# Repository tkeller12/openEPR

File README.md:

# openEPR
Open-Source EPR Spectrometer

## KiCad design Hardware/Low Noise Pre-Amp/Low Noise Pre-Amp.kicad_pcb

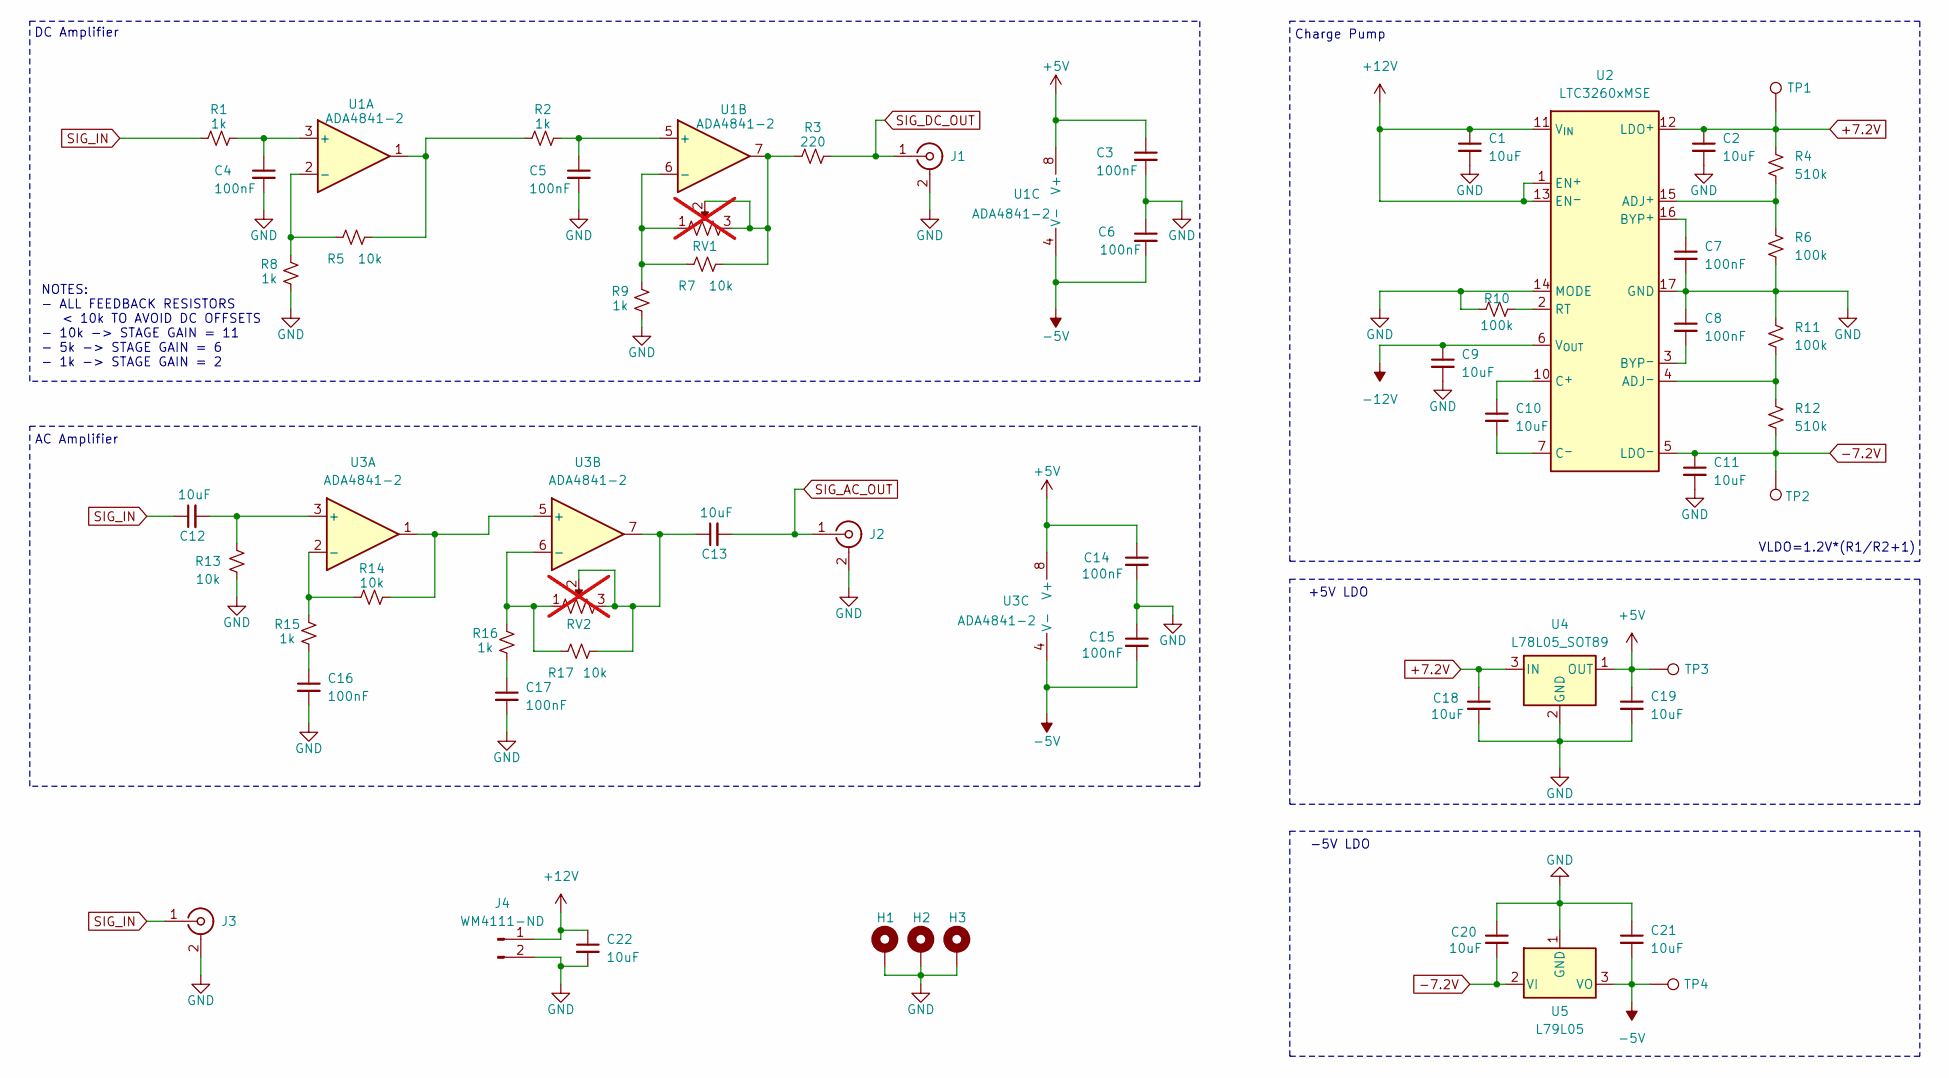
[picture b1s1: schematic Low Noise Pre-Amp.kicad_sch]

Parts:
C1, C2, C9, C10, C11, C12, C13, C18, C19, C20, C21, C22: 10uF; C_0805_2012Metric; MPN GRM21BR61H106KE43L; Digikey 490-18663-1-ND
C3, C4, C5, C6, C7, C8, C14, C15, C16, C17: 100nF; C_0805_2012Metric; MPN C0805C104K5RACTU; Digikey 399-C0805C104K5RACTUCT-ND
H1, H2, H3: M3; MountingHole_3.2mm_M3_DIN965_Pad
J1, J2, J3: RF2-152-T-00-50-G-HDW; SMA_Wurth_60312002114503_Vertical; MPN RF2-152-T-00-50-G-HDW; Digikey 2057-RF2-152-T-00-50-G-HDW-ND
J4: WM4111-ND; Molex_KK-254_AE-6410-02A_1x02_P2.54mm_Vertical; MPN 0022272021; Digikey WM4111-ND
R1, R2, R8, R9, R15, R16: 1k; R_0805_2012Metric; MPN RC0805FR-071KL; Digikey 311-1.00KCRCT-ND
R3: 220; R_0805_2012Metric; MPN RC0805FR-07220RL; Digikey 311-220CRCT-ND
R4, R12: 510k; R_0805_2012Metric; MPN RC0805FR-13510KL; Digikey 13-RC0805FR-13510KLCT-ND
R5, R7, R13, R14, R17: 10k; R_0805_2012Metric; MPN RC0805FR-0710KL; Digikey 311-10.0KCRCT-ND
R6, R10, R11: 100k; R_0805_2012Metric; MPN RC0805FR-07100KL; Digikey 311-100KCRCT-ND
RV1, RV2: R_Potentiometer_US; PinHeader_1x03_P2.54mm_Vertical; not fitted
TP1, TP2, TP3, TP4: TestPoint; TestPoint_Pad_D1.0mm
U1, U3: ADA4841-2; SOIC-8_3.9x4.9mm_P1.27mm; MPN ADA4841-2YRZ-R7; Digikey 505-ADA4841-2YRZ-R7CT-ND
U2: LTC3260xMSE; MSOP-16-1EP_3x4.039mm_P0.5mm_EP1.651x2.845mm_ThermalVias; MPN LTC3260EMSE#TRPBF; Digikey LTC3260EMSE#TRPBFCT-ND
U4: L78L05_SOT89; SOT-89-3; MPN L78L05ABUTR; Digikey 497-1181-1-ND
U5: L79L05; SOT-89-3; MPN L79L05ABUTR; Digikey 497-1217-1-ND

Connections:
+5V: C3.1, C14.1, C19.1, TP3.1, U1.8 (V+), U3.8 (V+), U4.1 (OUT)
+7.2V: C2.1, C18.1, R4.1, TP1.1, U2.12 (LDO^{+}), U4.3 (IN)
+12V: C1.1, C22.1, J4.1, U2.1 (EN^{+}), U2.11 (V_{IN}), U2.13 (EN^{-})
-5V: C6.2, C15.2, C21.2, TP4.1, U1.4 (V-), U3.4 (V-), U5.3 (VO)
-7.2V: C11.1, C20.2, R12.2, TP2.1, U2.5 (LDO^{-}), U5.2 (VI)
-12V: C9.1, U2.6 (V_{OUT})
GND: C1.2, C2.2, C3.2, C4.2, C5.2, C6.1, C7.2, C8.1, C9.2, C11.2, C14.2, C15.1, C16.2, C17.2, C18.2, C19.2, C20.1, C21.1, C22.2, H1.1, H2.1, H3.1, J1.2 (Ext), J2.2 (Ext), J3.2 (Ext), J4.2, R6.2, R8.1, R9.1, R10.2, R11.1, R13.1, U2.14 (MODE), U2.17 (GND), U4.2 (GND), U5.1 (GND)
unnamed: C13.1, R17.1, RV2.2, RV2.3, U3.7
unnamed: C16.1, R15.1
unnamed: C17.1, R16.1
unnamed: R2.1, R5.1, U1.1
unnamed: R3.1, R7.1, RV1.2, RV1.3, U1.7
unnamed: C4.1, R1.2, U1.3 (+)
unnamed: R5.2, R8.2, U1.2 (-)
unnamed: C5.1, R2.2, U1.5 (+)
unnamed: R7.2, R9.2, RV1.1, U1.6 (-)
unnamed: R4.2, R6.1, U2.15 (ADJ^{+})
unnamed: R11.2, R12.1, U2.4 (ADJ^{-})
unnamed: C7.1, U2.16 (BYP^{+})
unnamed: C8.2, U2.3 (BYP^{-})
unnamed: C10.1, U2.10 (C^{+})
unnamed: C10.2, U2.7 (C^{-})
unnamed: R10.1, U2.2 (RT)
unnamed: C12.2, R13.2, U3.3 (+)
unnamed: R14.1, R15.2, U3.2 (-)
unnamed: R14.2, U3.1, U3.5 (+)
unnamed: R16.2, R17.2, RV2.1, U3.6 (-)
SIG_AC_OUT: C13.2, J2.1 (In)
SIG_DC_OUT: J1.1 (In), R3.2
SIG_IN: C12.1, J3.1 (In), R1.1

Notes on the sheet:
+5V LDO
-5V LDO
Charge Pump
NOTES: - ALL FEEDBACK RESISTORS < 10k TO AVOID DC OFFSETS - 10k -> STAGE GAIN = 11 - 5k -> STAGE GAIN = 6 - 1k -> STAGE GAIN = 2
AC Amplifier
VLDO=1.2V*(R1/R2+1)
DC Amplifier

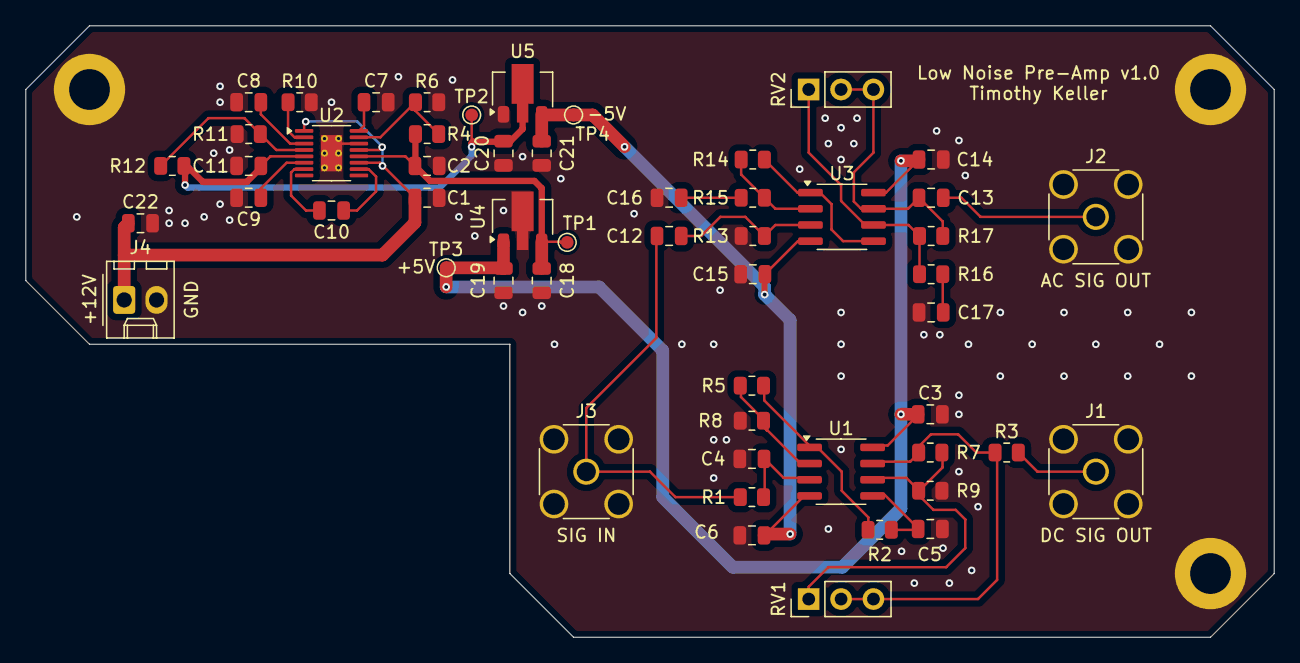
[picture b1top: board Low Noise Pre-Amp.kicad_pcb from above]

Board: 2 copper layers, 98.0 x 48.0 mm, 57 parts (0 on the bottom side), 30 nets.

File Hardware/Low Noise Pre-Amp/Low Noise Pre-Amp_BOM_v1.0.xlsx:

# | Reference | Qty | Value | DNP | Footprint | Description | Digikey | Manufacturer | MPN
1 | C1,C2,C9,C10,C11,C12,C13,C18,C19,C20,C21,C22 | 12 | 10uF |  | Capacitor_SMD:C_0805_2012Metric | Unpolarized capacitor, small symbol | 490-18663-1-ND | Murata Electronics | GRM21BR61H106KE43L
2 | C3,C4,C5,C6,C7,C8,C14,C15,C16,C17 | 10 | 100nF |  | Capacitor_SMD:C_0805_2012Metric | Unpolarized capacitor, small symbol | 399-C0805C104K5RACTUCT-ND | KEMET | C0805C104K5RACTU
3 | J1,J2,J3 | 3 | RF2-152-T-00-50-G-HDW |  | Connector_Coaxial:SMA_Wurth_60312002114503_Vertical | SMA JACK STR PCB 50OHM 18GHZ BRS | 2057-RF2-152-T-00-50-G-HDW-ND | Adam Tech | RF2-152-T-00-50-G-HDW
4 | J4 | 1 | WM4111-ND |  | Connector_Molex:Molex_KK-254_AE-6410-02A_1x02_P2.54mm_Vertical | CONN HEADER VERT 2POS 2.54MM | WM4111-ND | Molex | 0022272021
5 | R1,R2,R8,R9,R15,R16 | 6 | 1k |  | Resistor_SMD:R_0805_2012Metric | Resistor, small US symbol | 311-1.00KCRCT-ND | YAGEO | RC0805FR-071KL
6 | R3 | 1 | 220 |  | Resistor_SMD:R_0805_2012Metric | Resistor, small US symbol | 311-220CRCT-ND | YAGEO | RC0805FR-07220RL
7 | R4,R12 | 2 | 510k |  | Resistor_SMD:R_0805_2012Metric | Resistor, small US symbol | 13-RC0805FR-13510KLCT-ND | YAGEO | RC0805FR-13510KL
8 | R5,R7,R13,R14,R17 | 5 | 10k |  | Resistor_SMD:R_0805_2012Metric | Resistor, small US symbol | 311-10.0KCRCT-ND | YAGEO | RC0805FR-0710KL
9 | R6,R10,R11 | 3 | 100k |  | Resistor_SMD:R_0805_2012Metric | Resistor, small US symbol | 311-100KCRCT-ND | YAGEO | RC0805FR-07100KL
10 | RV1,RV2 | 2 | R_Potentiometer_US | DNP | Connector_PinHeader_2.54mm:PinHeader_1x03_P2.54mm_Vertical | Potentiometer, US symbol
11 | U1,U3 | 2 | ADA4841-2 |  | Package_SO:SOIC-8_3.9x4.9mm_P1.27mm | IC OPAMP GP 2 CIRCUIT 8SOIC | 505-ADA4841-2YRZ-R7CT-ND | Analog Devices Inc. | ADA4841-2YRZ-R7
12 | U2 | 1 | LTC3260xMSE |  | Package_SO:MSOP-16-1EP_3x4.039mm_P0.5mm_EP1.651x2.845mm_ThermalVias | IC REG CHARGE PUMP INV DL 16MSOP | LTC3260EMSE#TRPBFCT-ND | Analog Devices Inc. | LTC3260EMSE#TRPBF
13 | U4 | 1 | L78L05_SOT89 |  | Package_TO_SOT_SMD:SOT-89-3 | IC REG LINEAR 5V 100MA SOT89-3 | 497-1181-1-ND | STMicroelectronics | L78L05ABUTR
14 | U5 | 1 | L79L05 |  | Package_TO_SOT_SMD:SOT-89-3 | IC REG LINEAR -5V 100MA SOT89-3 | 497-1217-1-ND | STMicroelectronics | L79L05ABUTR

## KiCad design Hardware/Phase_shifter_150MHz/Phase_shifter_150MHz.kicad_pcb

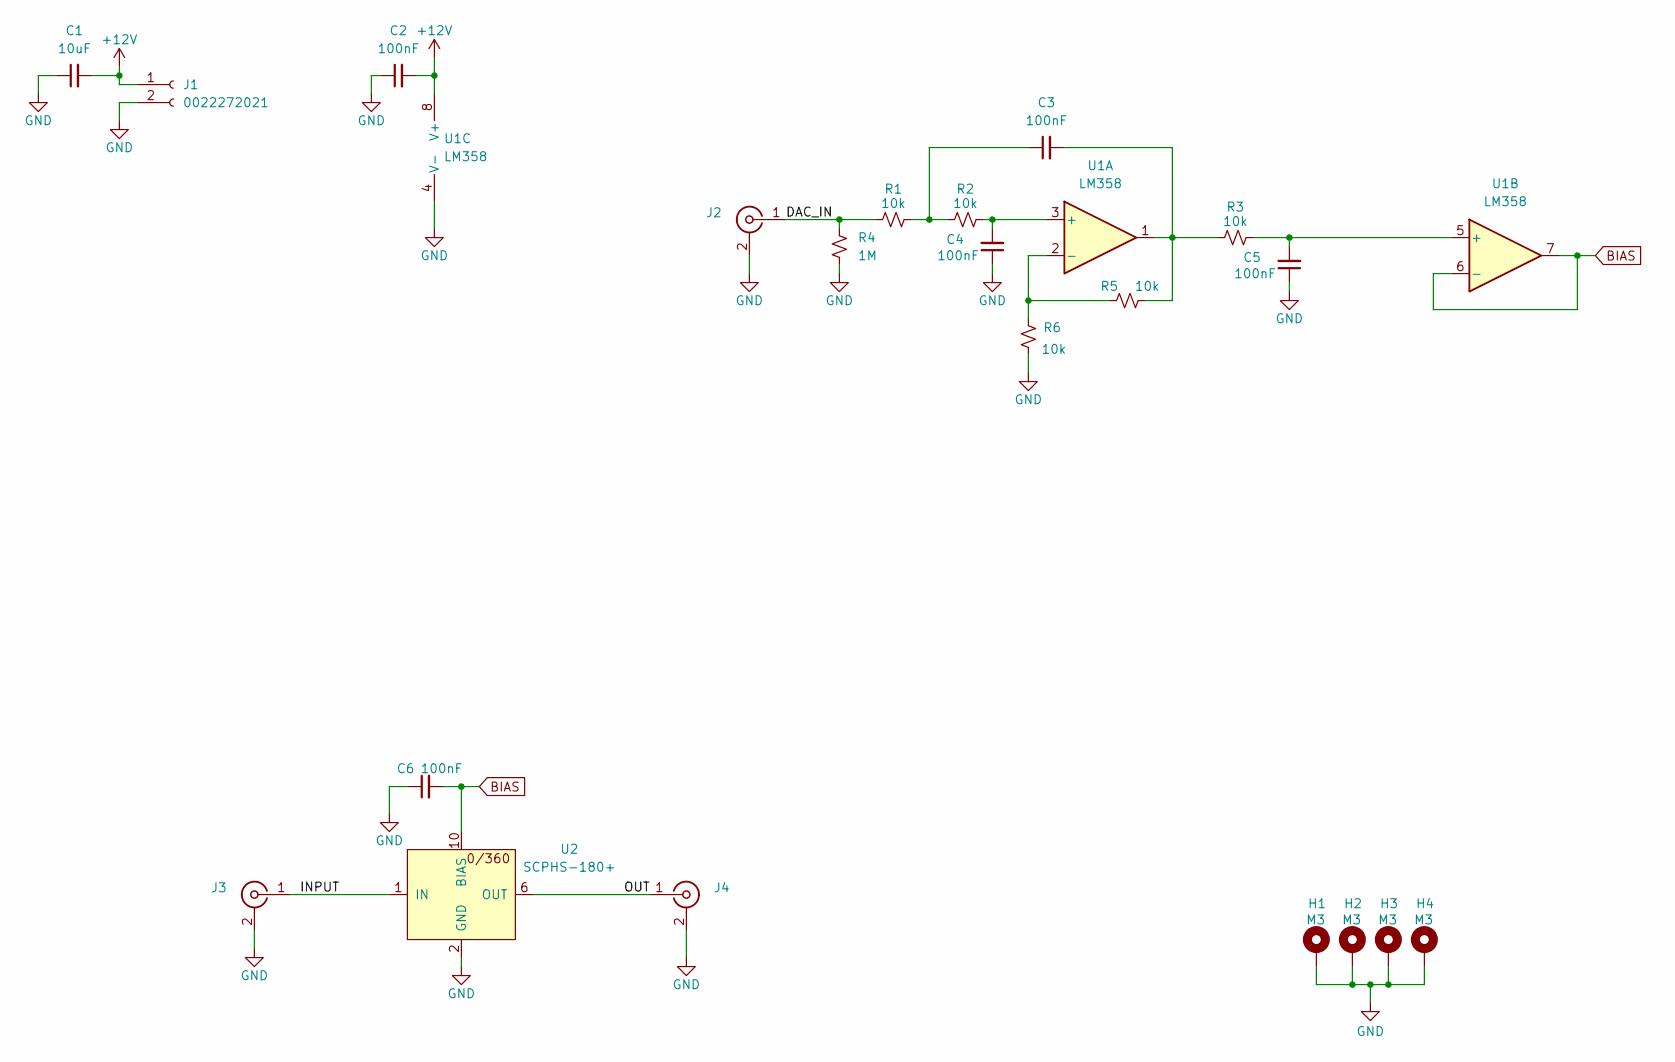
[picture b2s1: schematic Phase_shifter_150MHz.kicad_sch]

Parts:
C1: 10uF; C_0805_2012Metric; MPN 490-18663-1-ND; Digikey 490-18663-1-ND
C2, C3, C4, C5, C6: 100nF; C_0805_2012Metric; MPN C0805C104K5RACTU; Digikey 399-C0805C104K5RACTUCT-ND
H1, H2, H3, H4: M3; MountingHole_3.2mm_M3_DIN965_Pad
J1: 0022272021; Molex_KK-254_AE-6410-02A_1x02_P2.54mm_Vertical; MPN 0022272021; Digikey WM4111-ND
J2, J3, J4: SMA-J-P-H-ST-EM1; SMA_Samtec_SMA-J-P-H-ST-EM1_EdgeMount; MPN SMA-J-P-H-ST-EM1; Digikey SAM8857-ND
R1, R2, R3, R5, R6: 10k; R_0805_2012Metric; MPN RMCF0805FT10K0; Digikey RMCF0805FT10K0CT-ND
R4: 1M; R_0805_2012Metric; MPN RC0805FR-071ML; Digikey 311-1.00MCRCT-ND
U1: LM358; SOIC-8_3.9x4.9mm_P1.27mm; MPN LM358DR; Digikey 296-LM358DRCT-ND
U2: SCPHS-180+; MPN SCPHS-180+; Digikey 3157-SCPHS-180+-ND

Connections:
+12V: C1.2, C2.2, J1.1, U1.8 (V+)
/DAC_IN: J2.1 (In), R1.1, R4.1
/INPUT: J3.1 (In), U2.1 (IN)
/OUT: J4.1 (In), U2.6 (OUT)
BIAS: C6.2, U1.6 (-), U1.7, U2.10 (BIAS), U2.11 (BIAS)
GND: C1.1, C2.1, C4.1, C5.1, C6.1, H1.1, H2.1, H3.1, H4.1, J1.2, J2.2 (Ext), J3.2 (Ext), J4.2 (Ext), R4.2, R6.2, U1.4 (V-), U2.2 (GND), U2.3 (GND), U2.4 (GND), U2.5 (GND), U2.7 (GND), U2.8 (GND), U2.9 (GND), U2.12 (GND), U2.13 (GND), U2.14 (GND)
unnamed: C3.1, R1.2, R2.1
unnamed: C3.2, R3.1, R5.2, U1.1
unnamed: C4.2, R2.2, U1.3 (+)
unnamed: R5.1, R6.1, U1.2 (-)
unnamed: C5.2, R3.2, U1.5 (+)

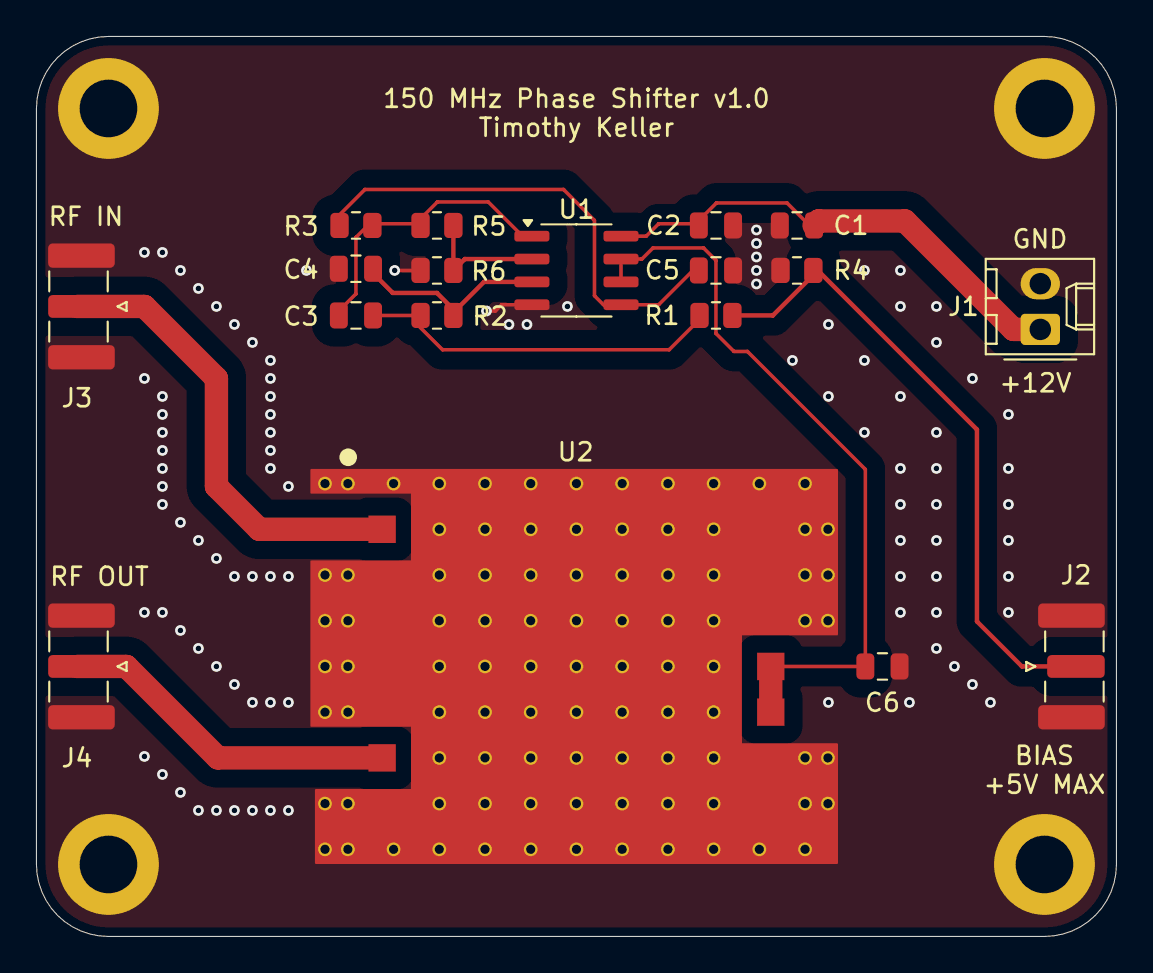
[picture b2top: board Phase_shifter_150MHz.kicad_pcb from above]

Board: 2 copper layers, 60.0 x 50.0 mm, 22 parts (0 on the bottom side), 11 nets.

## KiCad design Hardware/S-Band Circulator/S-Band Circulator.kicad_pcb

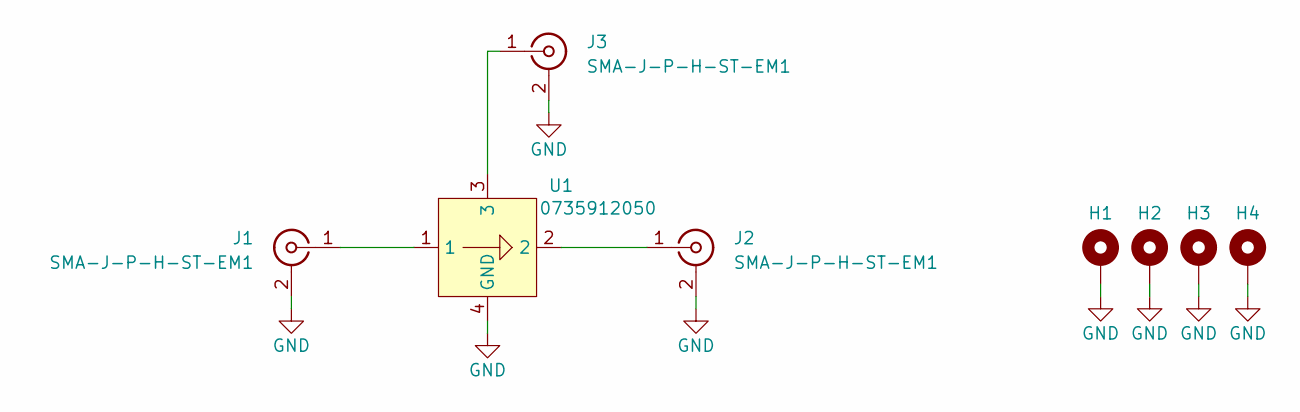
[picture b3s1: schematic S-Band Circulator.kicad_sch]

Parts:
H1, H2, H3, H4: 4-40; 4-40_Hole_Pad
J1, J2, J3: SMA-J-P-H-ST-EM1; SMA_Samtec_SMA-J-P-H-ST-EM1_EdgeMount; MPN SMA-J-P-H-ST-EM1; Digikey SAM8857-ND
U1: 0735912050; MPN 0735912050; Digikey 900-0735912050CT-ND

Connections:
GND: H1.1, H2.1, H3.1, H4.1, J1.2 (Ext), J2.2 (Ext), J3.2 (Ext), U1.4 (GND)
unnamed: J1.1 (In), U1.1
unnamed: J2.1 (In), U1.2
unnamed: J3.1 (In), U1.3

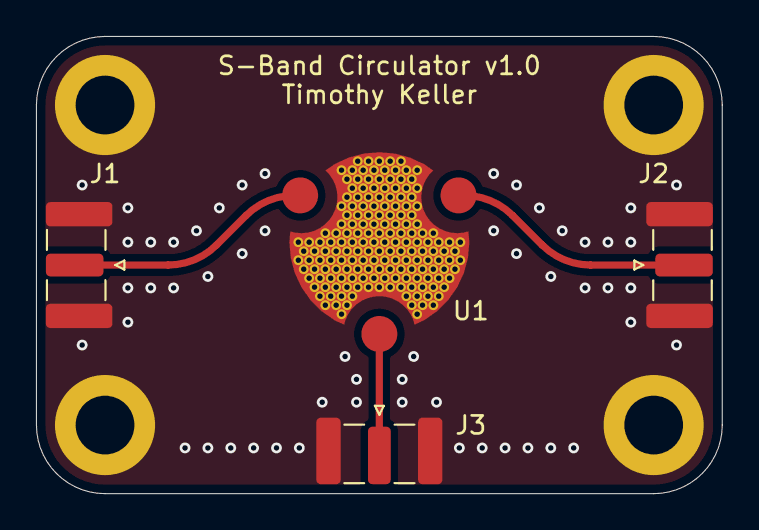
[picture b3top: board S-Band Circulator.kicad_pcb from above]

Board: 4 copper layers, 38.1 x 25.4 mm, 8 parts (0 on the bottom side), 4 nets.

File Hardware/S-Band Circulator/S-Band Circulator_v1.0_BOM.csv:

"Reference","Qty","Value","DNP","Footprint","Description","MPN","Manufacturer","Digikey"
"J1,J2,J3","3","SMA-J-P-H-ST-EM1","","Connector_Coaxial:SMA_Samtec_SMA-J-P-H-ST-EM1_EdgeMount","CONN SMA JACK STR 50OHM EDGE MNT","SMA-J-P-H-ST-EM1","Samtec Inc.","SAM8857-ND"
"U1","1","0735912050","","_tim-RF:0735912050","SMSJ CIRCULATOR/2300-2400","0735912050","Molex","900-0735912050CT-ND"

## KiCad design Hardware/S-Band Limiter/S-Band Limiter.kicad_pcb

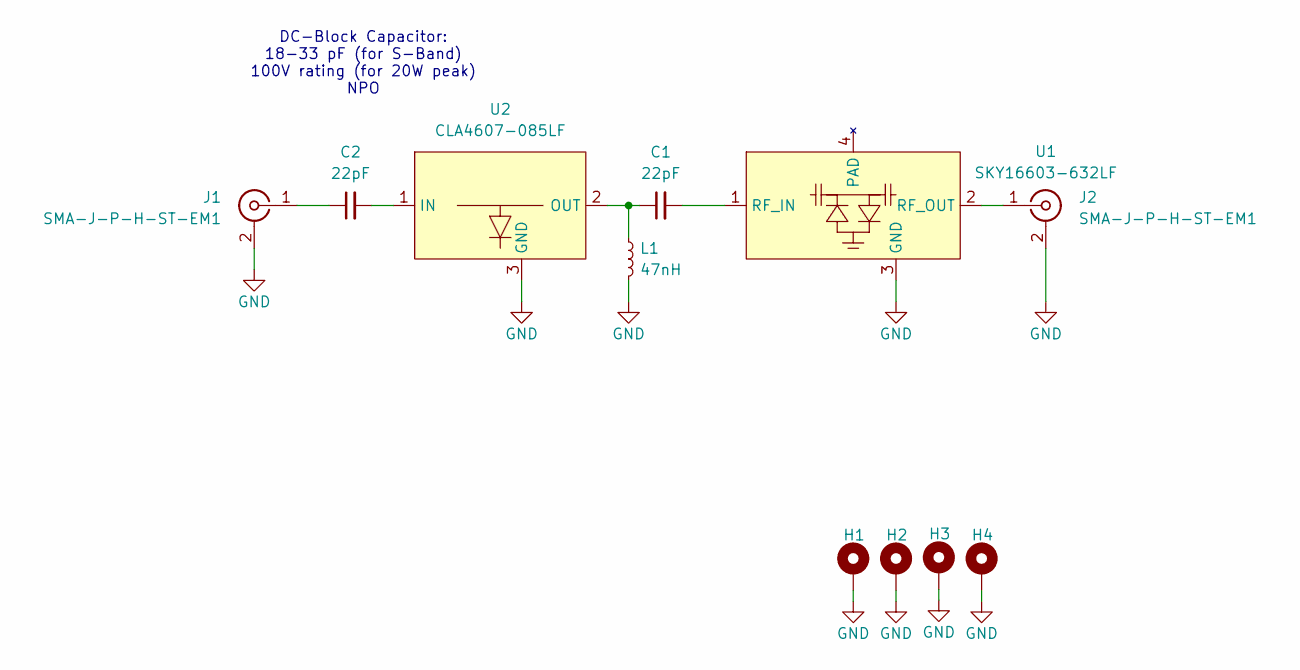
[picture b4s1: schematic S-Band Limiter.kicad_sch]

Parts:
C1, C2: 22pF; C_0402_1005Metric; MPN 600L220JT200T4K; Digikey 478-600L220JT200T4KCT-ND
H1, H2, H3, H4: 4-40; 4-40_Hole_Pad
J1, J2: SMA-J-P-H-ST-EM1; SMA_Samtec_SMA-J-P-H-ST-EM1_EdgeMount; MPN SMA-J-P-H-ST-EM1; Digikey SAM8857-ND
L1: 47nH; L_0402_1005Metric; MPN LQW15AN47NJ00D; Digikey 490-1154-1-ND
U1: SKY16603-632LF; DFN-2-2.3x2.3; MPN SKY16603-632LF; Digikey 863-SKY16603-632LFCT-ND
U2: CLA4607-085LF; QFN-2-1EP_2x2mm; MPN CLA4607-085LF; Digikey 863-2040-1-ND

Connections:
GND: H1.1, H2.1, H3.1, H4.1, J1.2 (Ext), J2.2 (Ext), L1.2, U1.3 (GND), U2.3 (GND)
unnamed: C2.1, J1.1 (In)
unnamed: J2.1 (In), U1.2 (RF_OUT)
unnamed: C1.2, U1.1 (RF_IN)
unnamed: C2.2, U2.1 (IN)
unnamed: C1.1, L1.1, U2.2 (OUT)

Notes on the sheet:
DC-Block Capacitor: 18-33 pF (for S-Band) 100V rating (for 20W peak) NPO

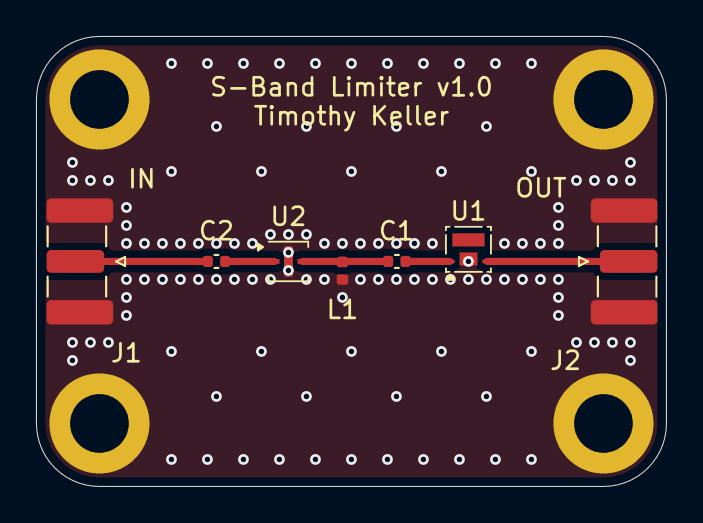
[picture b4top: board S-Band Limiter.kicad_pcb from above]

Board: 4 copper layers, 35.0 x 25.0 mm, 11 parts (0 on the bottom side), 6 nets.

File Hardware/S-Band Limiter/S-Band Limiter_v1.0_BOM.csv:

"Reference","Qty","Value","DNP","Footprint","MPN","Manufacturer","Digikey","Description"
"C1,C2","2","22pF","","Capacitor_SMD:C_0402_1005Metric","600L220JT200T4K","KYOCERA AVX","478-600L220JT200T4KCT-ND","Unpolarized capacitor, small symbol"
"H1,H2,H3,H4","4","4-40","","_tim-Mounting-Holes:4-40_Hole_Pad","","","","Mounting Hole with connection"
"J1,J2","2","SMA-J-P-H-ST-EM1","","Connector_Coaxial:SMA_Samtec_SMA-J-P-H-ST-EM1_EdgeMount","SMA-J-P-H-ST-EM1","Samtec Inc.","SAM8857-ND","coaxial connector (BNC, SMA, SMB, SMC, Cinch/RCA, LEMO, ...)"
"L1","1","47nH","","Inductor_SMD:L_0402_1005Metric","LQW15AN47NJ00D","Murata Electronics","490-1154-1-ND","Inductor, small symbol"
"U1","1","SKY16603-632LF","","_tim-RF:DFN-2-2.3x2.3","SKY16603-632LF","Skyworks Solutions Inc.","863-SKY16603-632LFCT-ND","High-Linearity Dual PIN Diode Limiter 0.6 to 6.0 GHz"
"U2","1","CLA4607-085LF","","_tim-RF:QFN-2-1EP_2x2mm","CLA4607-085LF","Skyworks Solutions Inc.","863-2040-1-ND","RF DIODE PIN 180V 13W 3QFN"

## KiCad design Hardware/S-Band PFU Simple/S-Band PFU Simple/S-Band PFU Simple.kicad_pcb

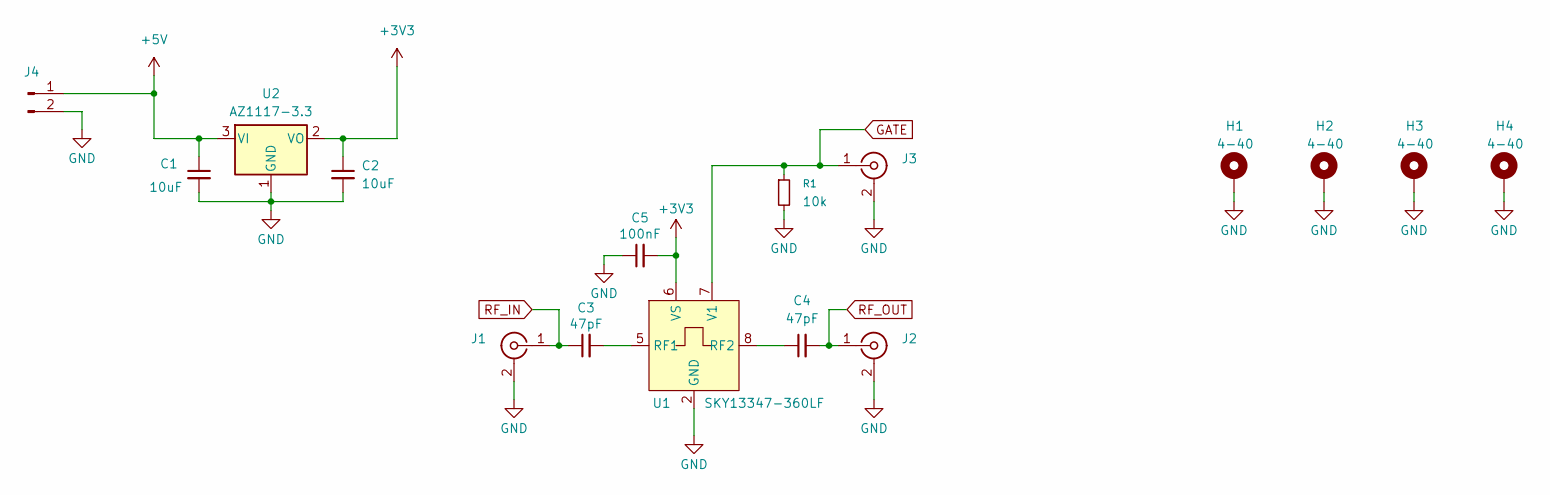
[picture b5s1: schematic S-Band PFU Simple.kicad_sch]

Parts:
C1, C2: 10uF; C_0805_2012Metric; MPN CL21A106KOQNNNG; Digikey 1276-6455-1-ND
C3, C4: 47pF; C_0402_1005Metric
C5: 100nF; C_0805_2012Metric; MPN KGM21NR71H104KT; Digikey 478-KGM21NR71H104KTCT-ND
H1, H2, H3, H4: 4-40; 4-40_Hole_Pad
J1, J2, J3: 2057-RF2-152-T-00-50-G-HDW-ND; SMA_Samtec_SMA-J-P-H-ST-EM1_EdgeMount; MPN SMA-J-P-H-ST-EM1; Digikey SAM8857-ND
J4: 61300211121; PinHeader_1x02_P2.54mm_Vertical; MPN 61300211121; Digikey 732-5315-ND
R1: 10k; R_0805_2012Metric; MPN CRCW080510K0FKEAC; Digikey 541-3976-1-ND
U1: SKY13347-360LF; DFN-8-1EP_2x2mm_P0.5mm_EP0.9x1.7mm; MPN SKY13347-360LF; Digikey 863-1457-1-ND
U2: AZ1117-3.3; SOT-223-3_TabPin2; MPN AZ1117CH-3.3TRG1; Digikey AZ1117CH-3.3TRG1DICT-ND

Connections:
+3V3: C2.1, C5.2, U1.6 (VS), U2.2 (VO)
+5V: C1.1, J4.1, U2.3 (VI)
GATE: J3.1 (In), R1.1, U1.7 (V1)
GND: C1.2, C2.2, C5.1, H1.1, H2.1, H3.1, H4.1, J1.2 (Ext), J2.2 (Ext), J3.2 (Ext), J4.2, R1.2, U1.1 (GND), U1.2 (GND), U1.3 (GND), U1.4 (GND), U1.9 (GND), U2.1 (GND)
unnamed: C3.2, U1.5 (RF1)
unnamed: C4.1, U1.8 (RF2)
RF_IN: C3.1, J1.1 (In)
RF_OUT: C4.2, J2.1 (In)

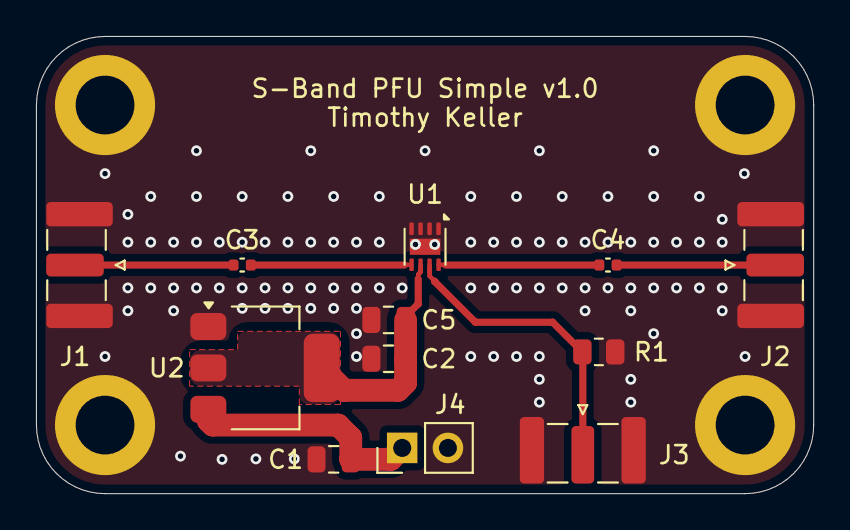
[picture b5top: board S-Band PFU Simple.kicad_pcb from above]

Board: 4 copper layers, 43.2 x 25.4 mm, 16 parts (0 on the bottom side), 8 nets.

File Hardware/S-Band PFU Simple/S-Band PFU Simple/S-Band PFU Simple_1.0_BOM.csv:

"Reference","Qty","Value","DNP","Exclude from BOM","Exclude from Board","Footprint","MPN","Manufacturer","Digikey","Description"
"C1,C2","2","10uF","","","","Capacitor_SMD:C_0805_2012Metric","CL21A106KOQNNNG","Samsung Electro-Mechanics","1276-6455-1-ND","CAP CER 10UF 16V X5R 0805"
"C3,C4","2","47pF","","","","Capacitor_SMD:C_0402_1005Metric","","","","CAP CER 47PF 50V C0G 0402"
"C5","1","100nF","","","","Capacitor_SMD:C_0805_2012Metric","KGM21NR71H104KT","KYOCERA AVX","478-KGM21NR71H104KTCT-ND","CAP CER 0.1UF 50V X7R 0805"
"J1,J2,J3","3","2057-RF2-152-T-00-50-G-HDW-ND","","","","Connector_Coaxial:SMA_Samtec_SMA-J-P-H-ST-EM1_EdgeMount","SMA-J-P-H-ST-EM1","Samtec Inc.","SAM8857-ND","CONN SMA JACK STR 50OHM EDGE MNT"
"J4","1","61300211121","","","","Connector_PinHeader_2.54mm:PinHeader_1x02_P2.54mm_Vertical","61300211121","Würth Elektronik","732-5315-ND","CONN HEADER VERT 2POS 2.54MM"
"R1","1","10k","","","","Resistor_SMD:R_0805_2012Metric","CRCW080510K0FKEAC","Vishay Dale","541-3976-1-ND","RES 10K OHM 1% 1/8W 0805"
"U1","1","SKY13347-360LF","","","","Package_DFN_QFN:DFN-8-1EP_2x2mm_P0.5mm_EP0.9x1.7mm","SKY13347-360LF","Skyworks Solutions Inc.","863-1457-1-ND","IC RF SWITCH SPST 3GHZ 8DFN"
"U2","1","AZ1117-3.3","","","","Package_TO_SOT_SMD:SOT-223-3_TabPin2","AZ1117CH-3.3TRG1","Diodes Incorporated","AZ1117CH-3.3TRG1DICT-ND","IC REG LINEAR 3.3V 1A SOT-223-3"

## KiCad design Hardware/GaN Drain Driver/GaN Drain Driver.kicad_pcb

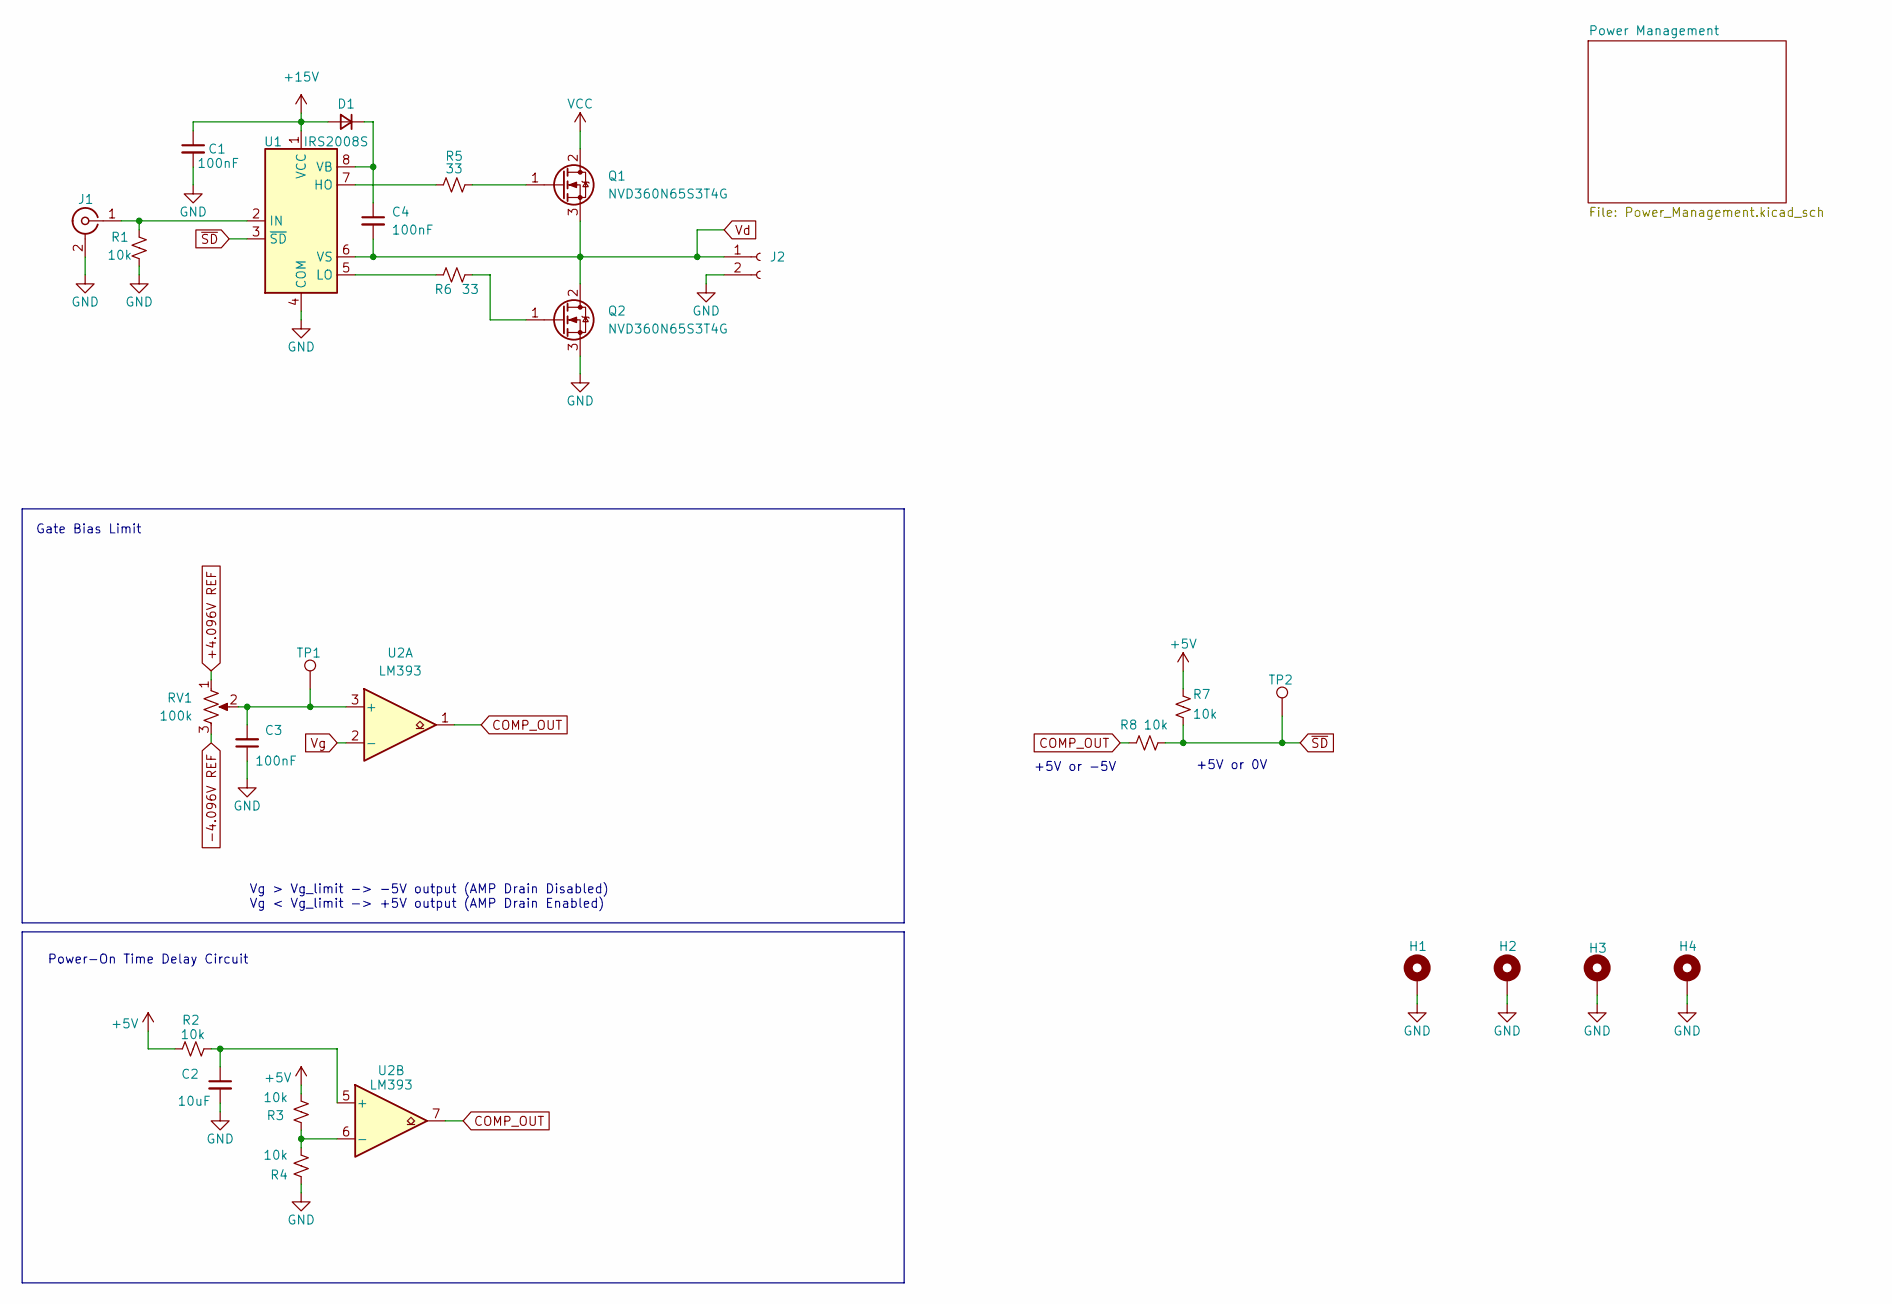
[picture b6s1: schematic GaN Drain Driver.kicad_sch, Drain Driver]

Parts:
C1, C3, C4: 100nF; C_0805_2012Metric; MPN KGM21NR71H104KT; Digikey 478-KGM21NR71H104KTCT-ND
C2: 10uF; C_0805_2012Metric; MPN CL21A106KAYNNNE; Digikey 1276-2891-1-ND
D1: 1N5819HW-7-F; D_SOD-123; MPN 1N5819HW-7-F; Digikey 1N5819HW-FDICT-ND
H1, H2, H3, H4: 4-40; 4-40_Hole_Pad
J1: SMA-J-P-H-ST-EM1; SMA_Samtec_SMA-J-P-H-ST-EM1_EdgeMount; MPN SMA-J-P-H-ST-EM1; Digikey SAM8857-ND
J2: 0022272021; Molex_KK-254_AE-6410-02A_1x02_P2.54mm_Vertical; MPN 0022272021; Digikey WM4111-ND
Q1, Q2: NVD360N65S3T4G; TO-252-2; MPN NVD360N65S3T4G; Digikey 488-NVD360N65S3T4GCT-ND
R1, R2, R3, R4, R7, R8: 10k; R_0805_2012Metric; MPN CRCW080510K0FKEAC; Digikey 541-3976-1-ND
R5, R6: 33; R_0805_2012Metric; MPN RC0805FR-0733RL; Digikey 311-33.0CRCT-ND
RV1: 100k; Potentiometer_Bourns_3296W_Vertical; MPN PV36W104C01B00; Digikey 118-PV36W104C01B00-ND
TP1, TP2: TestPoint; TestPoint_Pad_D1.0mm
U1: IRS2008S; SOIC-8_3.9x4.9mm_P1.27mm; MPN IRS2008STRPBF; Digikey IRS2008STRPBFCT-ND
U2: LM393; SOIC-8_3.9x4.9mm_P1.27mm; MPN LM393DT; Digikey 497-1593-1-ND

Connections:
+4.096V REF: RV1.1; also elsewhere on the board
+5V: R2.1, R3.2, R7.1; also elsewhere on the board
+15V: C1.1, D1.2 (A), U1.1 (VCC); also elsewhere on the board
-4.096V REF: RV1.3; also elsewhere on the board
COMP_OUT: R8.1, U2.1, U2.7
GND: C1.2, C2.2, C3.1, H1.1, H2.1, H3.1, H4.1, J1.2 (Ext), J2.2, Q2.3 (S), R1.2, R4.1, U1.4 (COM); also elsewhere on the board
unnamed: C4.1, D1.1 (K), U1.8 (VB)
unnamed: J1.1 (In), R1.1, U1.2 (IN)
unnamed: Q1.1 (G), R5.2
unnamed: Q2.1 (G), R6.2
unnamed: R5.1, U1.7 (HO)
unnamed: R6.1, U1.5 (LO)
unnamed: C3.2, RV1.2, TP1.1, U2.3 (+)
unnamed: C2.1, R2.2, U2.5 (+)
unnamed: R3.1, R4.2, U2.6 (-)
VCC: Q1.2 (D); also elsewhere on the board
Vd: C4.2, J2.1, Q1.3 (S), Q2.2 (D), U1.6 (VS)
Vg: U2.2 (-); also elsewhere on the board
~SD: R7.2, R8.2, TP2.1, U1.3 (~SD)

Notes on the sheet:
Vg > Vg_limit -> -5V output (AMP Drain Disabled) Vg < Vg_limit -> +5V output (AMP Drain Enabled)
+5V or -5V
+5V or 0V
Power-On Time Delay Circuit
Gate Bias Limit
